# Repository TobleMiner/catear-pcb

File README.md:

Nekomimi PCB
============

This repo contains the PCB for the Nekomimi project of @BenBE . It will be used
to illuminate 3D printed catears.

This is a short Video of two RevA circuit boards wired up for testing:  

# PCB top

# PCB bottom

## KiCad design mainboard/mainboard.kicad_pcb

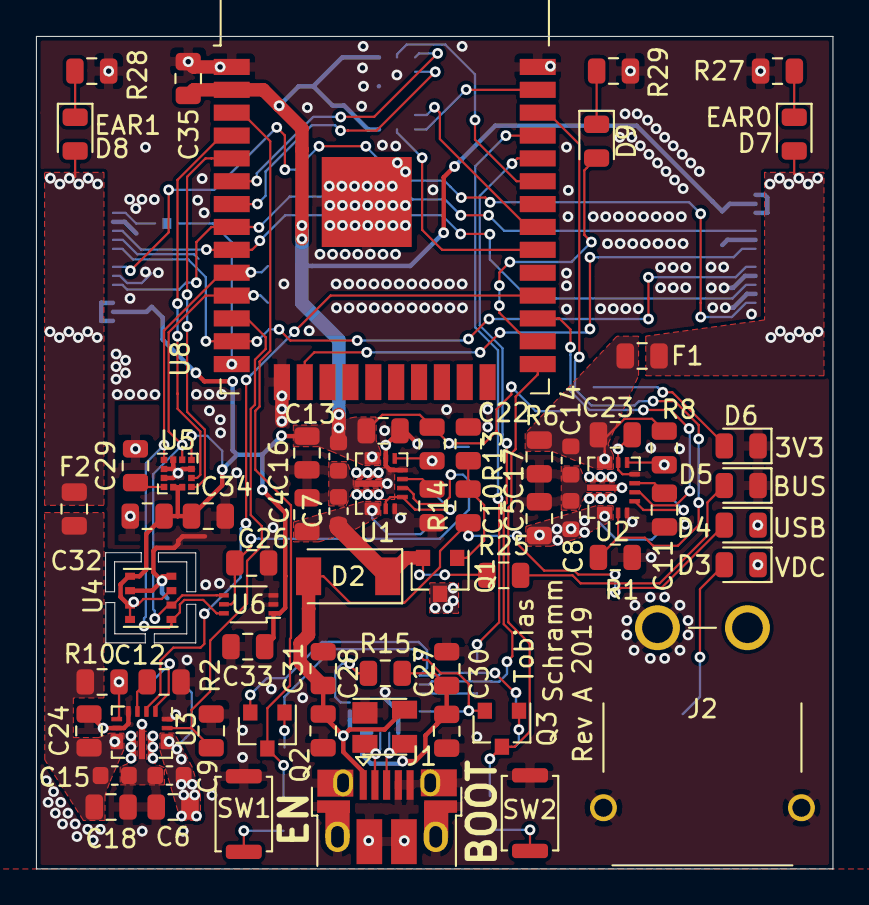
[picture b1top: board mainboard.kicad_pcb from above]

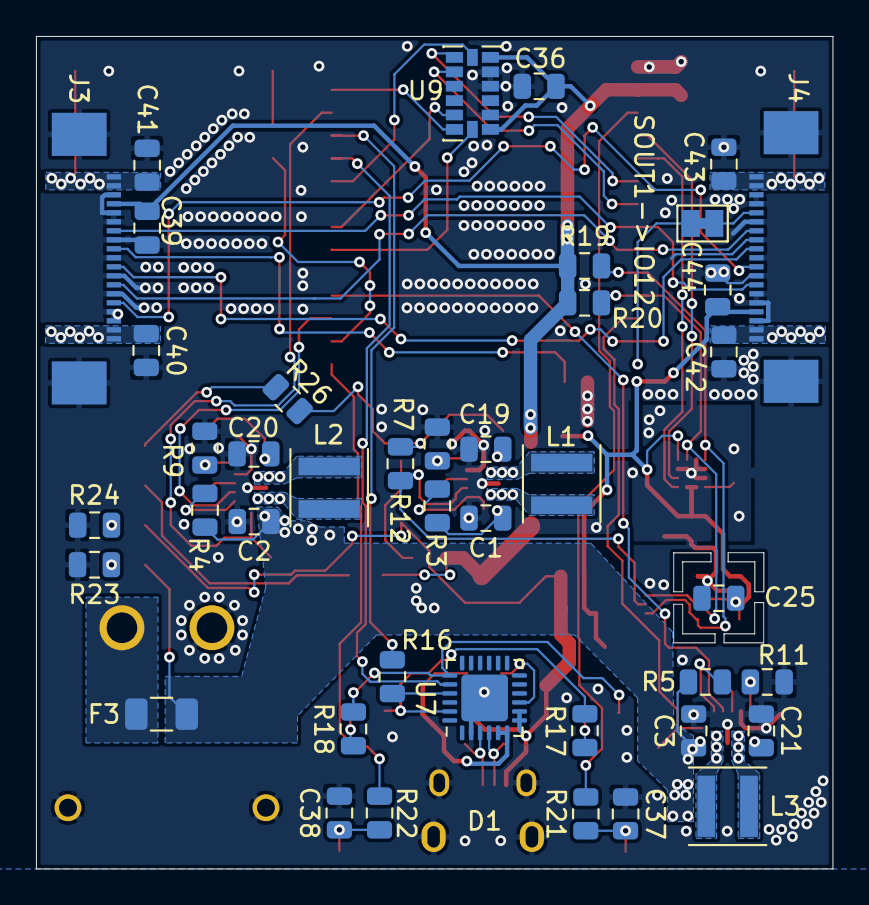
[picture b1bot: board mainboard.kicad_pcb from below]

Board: 2 copper layers, 44.3 x 46.2 mm, 107 parts (42 on the bottom side), 72 nets.

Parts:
C1, C2, C3, C4, C5, C6, C16, C17, C18, C19, C20, C21, C22, C23, C24, C27, C28, C30, C31, C35, C39, C40, C41, C42, C43, C44: C; C_0805_2012Metric
C7, C8, C9, C13, C14, C15: C; C_0603_1608Metric
C10, C11, C12, C25, C29, C32, C33, C36: 100 nC; C_0805_2012Metric
C26, C34: 1 uC; C_0805_2012Metric
C37, C38: 1 nC; C_0805_2012Metric
D1: SP0503BAHT; SOT-143
D2: PMEG3050EP,115; SOD-128-2
D3, D4, D5, D6, D7, D8, D9: LED; LED_0805_2012Metric
F1, F2: Fuse; Fuse_0805_2012Metric
F3: Fuse; Fuse_1206_3216Metric
J1: USB_B_Micro; USB_Micro-B_Amphenol_10103594-0001LF_Horizontal
J2: Conn_01x02_MountingPin; XT30PW
J3, J4: Conn_01x19_MountingPin; Molex_Easy-On_52746-1971_1x19_P0.5mm_Horizontal
JP1: Jumper; SolderJumper-2_P1.3mm_Bridged_Pad1.0x1.5mm
L1, L2, L3: L; L_Coilcraft_XxL4020
Q1: DMG2301L; SOT-23
Q2, Q3: MMBT3904; SOT-23
R1, R2, R3, R4, R5, R12: 10 kR; R_0805_2012Metric
R6, R8, R10: 470 kR; R_0805_2012Metric
R7: 150 kR; R_0805_2012Metric
R9, R11: 120 kR; R_0805_2012Metric
R13: 100 kR; R_0805_2012Metric
R14, R23, R25: 1 kR; R_0805_2012Metric
R15: 4.7 kR; R_0805_2012Metric
R16, R21, R22, R27, R28: 470 R; R_0805_2012Metric
R17, R18: 12 kR; R_0805_2012Metric
R19, R20: 2.2 kR; R_0805_2012Metric
R24: 330 R; R_0805_2012Metric
R26, R29: 220 R; R_0805_2012Metric
SW1, SW2: SW_Push; SW_Push_SPST_NO_Alps_SKRK
U1, U2, U3: tps63070; VQFN-HR-15
U4: BME680; Bosch_LGA-8_3x3mm_P0.8mm_ClockwisePinNumbering
U5: LIS3MDL; LGA-12_2x2mm_P0.5mm
U6: BH1750FVI; WSOF6I
U7: CP2102N-A01-GQFN24; QFN-24-1EP_4x4mm_P0.5mm_EP2.6x2.6mm
U8: ESP32-WROOM-32
U9: ADXL343; LGA-14_3x5mm_P0.8mm_LayoutBorder1x6y

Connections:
+3V3: C13.1, C16.1, C19.1, C22.1, C25.1, C32.1, C33.1, C34.1, C35.1, C36.1, C39.1, C44.1, J3.4, J4.4, R6.2, R12.1, R19.1, R20.1, R26.1, U1.7, U4.2, U4.5, U4.6, U4.8, U5.5, U5.6, U5.10, U6.1, U8.2, U9.1, U9.6
/D+: D1.3, J1.3, U7.3
/D-: D1.2, J1.2, U7.4
/DRDY: U5.8, U8.4
/DTR: Q3.2, R17.2, U7.23
/EN: Q2.3, R21.2, U8.3
/GSCLK: J3.7, J4.7, U8.8
/INT: U5.7, U8.5
/INT1: U8.6, U9.8
/INT2: U8.7, U9.9
/IO0: Q3.3, R22.2, U8.25
/IO4: D9.2, U8.26
/LAT: J3.13, J4.13, U8.9
/MISO: U8.31, U9.12
/MOSI: U8.37, U9.13
/PG_3V3: C26.1, R12.2, U1.2, U6.5
/PG_VCC0: U2.2, U8.27
/PG_VCC1: U3.2, U8.28
/RTS: Q2.2, R18.2, U7.19
/RXD: U7.20, U8.34
/SCK: U8.30, U9.14
/SCL: R19.2, U4.4, U5.1, U6.6, U8.10
/SCLK: J3.11, J4.11, U8.13
/SDA: R20.2, U4.3, U5.11, U6.4, U8.11
/SIN0: J3.9, U8.16
/SOUT0: J3.15, J4.9
/SOUT1: J4.15, JP1.2
/TXD: R16.1, U8.35
/VCC0_EN: R1.1, U2.14, U8.36
/VCC1_EN: R2.1, U3.14, U8.12
/~CS_ACCEL: U8.33, U9.7
GND: C1.2, C2.2, C3.2, C4.2, C5.2, C6.2, C7.2, C8.2, C9.2, C10.2, C11.2, C12.2, C13.2, C14.2, C15.2, C16.2, C17.2, C18.2, C19.2, C20.2, C21.2, C22.2, C23.2, C24.2, C25.2, C26.2, C27.2, C28.2, C29.2, C30.2, C31.2, C32.2, C33.2, C34.2, C35.2, C36.2, C37.1, C38.1, C39.2, C40.2, C41.2, C42.2, C43.2, C44.2, D1.1, D5.1, D6.1, J1.4, J1.5, J1.6, J2.2, J2.MP, J3.3, J3.5, J3.6, J3.8, J3.10, J3.12, J3.14, J3.16, J3.17, J3.MP, J4.3, J4.5, J4.6, J4.8, J4.10, J4.12, J4.14, J4.16, J4.17, J4.MP, R1.2, R2.2, R7.2, R9.2, R11.2, R13.2, R23.2, R24.2, R27.2, R28.2, R29.2, SW1.2, SW2.2, U1.4, U1.6, U1.10, U1.15, U2.4, U2.6, U2.10, U2.15, U3.4, U3.6, U3.10, U3.15, U4.1, U4.7, U5.2, U5.3, U5.9, U5.12, U6.2, U6.3, U7.2, U7.25, U8.1, U8.15, U8.38, U8.39, U9.2, U9.4, U9.5
unnamed: C10.1, U1.3
unnamed: C11.1, U2.3
unnamed: C12.1, U3.3
unnamed: C14.1, C17.1, C20.1, C23.1, F1.2, R8.2, U2.7
unnamed: C15.1, C18.1, C21.1, C24.1, F2.2, R10.2, U3.7
unnamed: C27.1, C30.1, R15.2, U7.5, U7.6
unnamed: C29.1, U5.4
unnamed: C37.2, R21.1, SW1.1
unnamed: C38.2, R22.1, SW2.1
unnamed: D3.1, R23.1
unnamed: D4.1, R24.1
unnamed: D5.2, R25.2
unnamed: D6.2, R26.2
unnamed: D7.1, R27.1
unnamed: D8.1, R28.1
unnamed: D9.1, R29.1
unnamed: F3.2, J2.1
unnamed: JP1.1, U8.14
unnamed: L1.1, U1.11
unnamed: L1.2, U1.9
unnamed: L2.1, U2.11
unnamed: L2.2, U2.9
unnamed: L3.1, U3.11
unnamed: L3.2, U3.9
unnamed: Q1.1, R13.1, R14.2
unnamed: Q2.1, R17.1
unnamed: Q3.1, R18.1
unnamed: R3.1, U1.1, U1.14
unnamed: R4.1, U2.1
unnamed: R5.1, U3.1
unnamed: R6.1, R7.1, U1.5
unnamed: R8.1, R9.1, U2.5
unnamed: R10.1, R11.1, U3.5
unnamed: R15.1, U7.9
unnamed: R16.2, U7.21
VBUS: C1.1, C4.1, C7.1, D2.1, Q1.2, R3.2, R25.1, U1.12
VCC_EAR0: C40.1, C41.1, D7.2, F1.1, J3.1, J3.2, J3.18, J3.19
VCC_EAR1: C42.1, C43.1, D8.2, F2.1, J4.1, J4.2, J4.18, J4.19
VDC: C2.1, C3.1, C5.1, C6.1, C8.1, C9.1, D3.2, F3.1, Q1.3, R4.2, R5.2, U2.12, U3.12
VUSB: C28.1, C31.1, D1.4, D2.2, D4.2, J1.1, R14.1, U7.7, U7.8

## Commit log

2019-03-25 Add LEDs and drivers
2019-03-25 Route (sort of) clock and data bus
2019-03-25 Route
2019-03-25 Add some bypass capacitance
2019-03-25 Add GND supports to GND net
2019-03-28 Partial reroute
2019-03-28 Reroute finised
2019-03-28 Ignore rendered gerbers
2019-03-28 Add additional VIA stitching and bypass capacitance
2019-03-28 Add mounting hole
2019-03-28 Add mounting holes
2019-03-28 Add silkscreen designators
2019-04-11 Switch to LEDs with integrated controller
2019-04-11 Lay out essential LEDs
2019-04-11 Route new layout
2019-04-11 Add thermal vias
2019-04-11 Add connector mounting pins to MP pad and connect them to VCC
2019-04-11 Remove connector holder PCB symbol
    There is already a variant with mounting pin
2019-04-11 Remove superfluous vertices from back groundplane
2019-04-11 Make base shape of backside groundplane rectangular
2019-04-11 Add left upper D19 LED
2019-04-11 Move silkscreen designators to unobstructed places
2019-04-11 Change revision designator to `Rev B`
2019-04-11 Add BenBes avatar to PCB
2019-04-11 Re-fill all floodfill areas
2019-04-27 Almost (tm) finish full rerouting
2019-04-27 Finish layouting
2019-04-27 Adjust UV LED attachment + U1 LED routing slightly
    Slight changes for better groundplane coverage
2019-04-27 More GND VIA stitching
2019-04-27 Pull down bottom center GND plane a little
    Fixes MP of flatflex connector reporting as not connected
2019-04-27 Move build year off of VIAs
2019-04-27 Move silkscreen component designators to unobstructed places
2019-04-27 Switch to more readily available Molex Easy-On 52746 series FFC
2019-04-27 Move up FFC slightly
    Ensures that pads won't be damaged when milling the PCB
2019-04-27 Move design year away from VIAs
2019-04-27 Remove stray via
2019-04-27 Maximize groundplane cooling capacity on U1
2019-04-27 Reroute GSSOUT and DCSOUT to optimize cooling of U2
2019-04-27 Add additional via stitching to GND of U2
2019-04-27 Add via stitching to low-impedance cap GNDs
2019-04-27 Remove info cache
2019-04-27 Ignore fp-info-cache
2019-04-28 Add LICENSE
2019-04-28 Add minimal README
2019-04-29 Add short clip of active RevA pair
2019-04-29 Force animation to wrap to next line
2019-05-02 Design revision D
2019-05-02 Revise connector layout
2019-05-02 Readjust silkscreen designators
2019-05-02 Remove obsolete measurement
2019-05-02 Hide silkscreen designators of mounting holes
2019-05-02 Add Artwork
2019-05-02 Add artwork attribution
2019-05-03 Optimize GND via stitching
2019-05-03 Add TP to unused TLC pin
2019-05-03 Readjust silkscreen designators around TP1
2019-05-03 Reassign component references
2019-05-03 Move D5 designator to a more convenient place
2019-05-03 Reroute U1_B9
2019-05-03 Move D18 VCC via to center of VCC pad
2019-05-07 Add LED 3D models
2019-05-07 Add RevD screenshots
2019-05-07 Add 3d connector model
2019-05-07 Use custom LED footprint with associated 3D model
2019-05-07 Update PCB renders
2019-05-09 Fix LED footprint
2019-05-09 Fix RGB LED routing
2019-05-09 RevE
2019-05-27 Make references from README relative
2019-06-04 Convert to panelizeable PCB
2019-06-04 Finish panel
2019-06-06 Move ears to separate directory
2019-06-06 Mainboard WIP
2019-06-06 Add basic circuitry
2019-06-06 Add sensors
2019-06-07 Add accelerometer and magnetometer
2019-06-07 Layouting WIP
2019-06-07 Assemble regulator sections
2019-06-08 Move components to sane-ish positions
2019-06-08 Separate switchmode regulator power and digital ground
2019-06-08 Add right-angle XT30 power connector
2019-06-08 More WIP
2019-06-08 Yet more WIP
2019-06-08 Finish basic routing
2019-06-08 More GND stitching
2019-06-08 Adjust silkscreen designators for readability
2019-06-08 Connect XT30 mounting pins to ground
2019-06-08 Fix designator of R29
2019-06-08 Reassign silkscreen designators
2019-06-09 More ground stitching
2019-06-09 Add revision indicator
2019-06-09 Create first PCB pair
2019-06-09 Add second pair of PCBs
2019-06-09 Add allignment holes
2019-06-09 Add mouse bites
2019-06-09 Ignore fab files
2019-06-09 Trim PCB to 100 x 100 mm
2019-06-10 Fix position of USB socket on upper boards
2019-07-13 Ignore all fab directories
2019-07-13 Replace reset circuitry
    It was the reference circuit used on the DevKitC V4 but it just plain does not work.
    Replaced by much simpler and more reliable design.
2019-07-24 Revert "Replace reset circuitry"
    This reverts commit 4aa51ba1305b71722c80cb68cdfb79191ae487c4.
    CP2102N defaults to RTS + CTS high. Thus the reference reset circuitry is the only
    simple way to make this work
2019-07-24 Add ~RESET pullup
2019-07-24 Add WROOM-32 with GND pad
2019-07-24 Swap RXD and TXD
2019-07-24 Adjust LED resistors for less eye piercing brightness
    Green LEDs really are bright. Reduce current to ~300 µA
2019-07-24 Add VDC voltage measurement divider
2019-07-24 Optimize ground
2019-07-24 Add pdm microphone
2019-07-24 Improve separation between I2S_CLK and I2S_DATA
2019-07-24 Improve GND impedance around U10
2019-07-24 More via stitching
2019-07-24 Add VDC input protection
2019-07-24 Fix inconsistent designator rotation
2019-07-29 Replace magnetometer by MC6470
2019-07-29 Start integration of BNO055
2019-07-29 Finish interation of BNO055
2019-07-29 Replace accelerometer by BNO055
2019-07-30 Move R34 to bottom layer
2019-08-01 Add measurements for 3d case
2019-08-05 More measurements for top
2019-08-05 Even more measurements for reduced readability
